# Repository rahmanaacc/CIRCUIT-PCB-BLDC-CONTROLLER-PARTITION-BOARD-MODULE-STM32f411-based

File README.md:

# Modular BLDC Motor Controller Partition Board (STM32F411CEU6 Based)

Projek Capstone ini berfokus pada perancangan hardware modul *controller* motor BLDC (Brushless DC) berbasis mikrokontroler **STM32F411CEU6** menggunakan metode kontrol **6-step commutation (trapezoidal control)**. 

Arsitektur hardware dirancang secara modular (*partition board*) dengan memisahkan domain sinyal kendali, *gate driver*, dan tingkat daya (*inverter stage*). Pemisahan topologi ini bertujuan untuk meminimalkan *noise* switching (EMI), mengoptimalkan manajemen termal, serta mempermudah proses pengujian dan *troubleshooting* secara independen pada tiap modul.

---

## Modul Hardware Utama

Repository ini terdiri dari tiga modul papan terpisah (*partition boards*):

1. **Control-MCU Module (`Control-MCU With Voltage Drop Detector 0,5mm`)**
   * Modul pemroses utama berbasis mikrokontroler **STM32F411CEU6**.
   * Dilengkapi rangkaian *Voltage Drop Detector* dengan lebar jalur *trace* teroptimasi 0,5 mm untuk menjaga integritas sinyal dan stabilitas tegangan referensi MCU.
   * Berfungsi mengolah algoritma **6-step commutation**, membaca sinyal *feedback* posisi rotor, dan menghasilkan sinyal PWM transmisi ke *gate driver*.

2. **Driver & Switching Optimization Circuit (`DRIVER and SWITCHING OPTIMIZATION CIRCUIT REV 2`)**
   * Modul perantara *gate driver* yang mengisolasi sinyal logika kendali level rendah dari tegangan tinggi *inverter*.
   * Mengintegrasikan rangkaian optimasi *switching* untuk mempercepat *rise/fall time* MOSFET, mengurangi *switching loss*, dan mencegah kondisi *cross-conduction* (*shoot-through*).

3. **Inverter Circuit (`INVERTER CIRCUIT REV 2 FIX`)**
   * Modul tingkat daya (*power stage*) berupa jembatan tiga fasa (*three-phase bridge inverter*).
   * Didesain untuk menangani arus tinggi dengan penataan jalur *copper pour* teroptimasi dan konektivitas daya fasa motor yang andal.

---

## Struktur Repository

```text
CIRCUIT-PCB-BLDC-CONTROLLER-PARTITION-BOARD-MODULE-STM32f411-based/
│
├── Control-MCU With Voltage Drop Detector 0,5mm/
│   ├── Control-MCU.kicad_sch          # Skematik KiCad Modul MCU
│   ├── Control-MCU.kicad_pcb          # Layout PCB Modul MCU
│   └── Control-MCU.kicad_pro          # Berkas Proyek KiCad Modul MCU
│
├── DRIVER and SWITCHING OPTIMIZATION CIRCUIT REV 2/
│   ├── DRIVER and SWITCHING OPTIMIZATION CIRCUIT.kicad_sch
│   ├── DRIVER and SWITCHING OPTIMIZATION CIRCUIT.kicad_pcb
│   └── DRIVER and SWITCHING OPTIMIZATION CIRCUIT.kicad_pro
│
├── INVERTER CIRCUIT REV 2 FIX/
│   ├── INVERTER CIRCUIT REV 2 FIX.kicad_sch
│   ├── INVERTER CIRCUIT REV 2 FIX.kicad_pcb
│   └── INVERTER CIRCUIT REV 2 FIX.kicad_pro
│
└── README.md

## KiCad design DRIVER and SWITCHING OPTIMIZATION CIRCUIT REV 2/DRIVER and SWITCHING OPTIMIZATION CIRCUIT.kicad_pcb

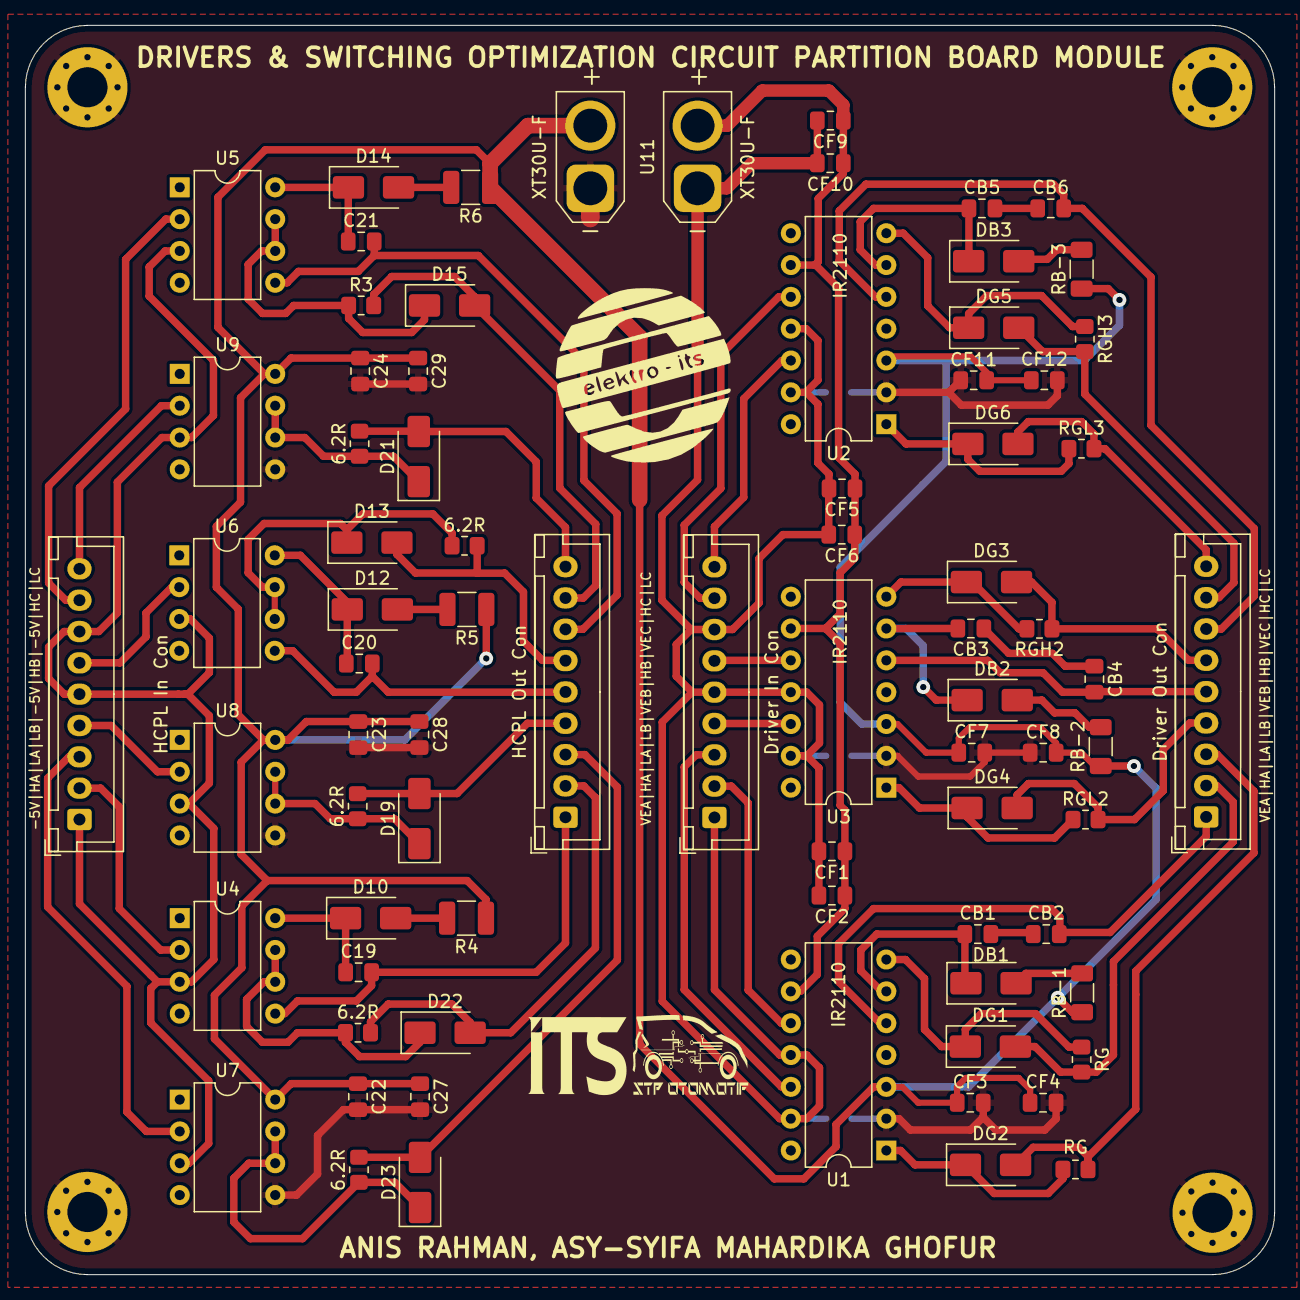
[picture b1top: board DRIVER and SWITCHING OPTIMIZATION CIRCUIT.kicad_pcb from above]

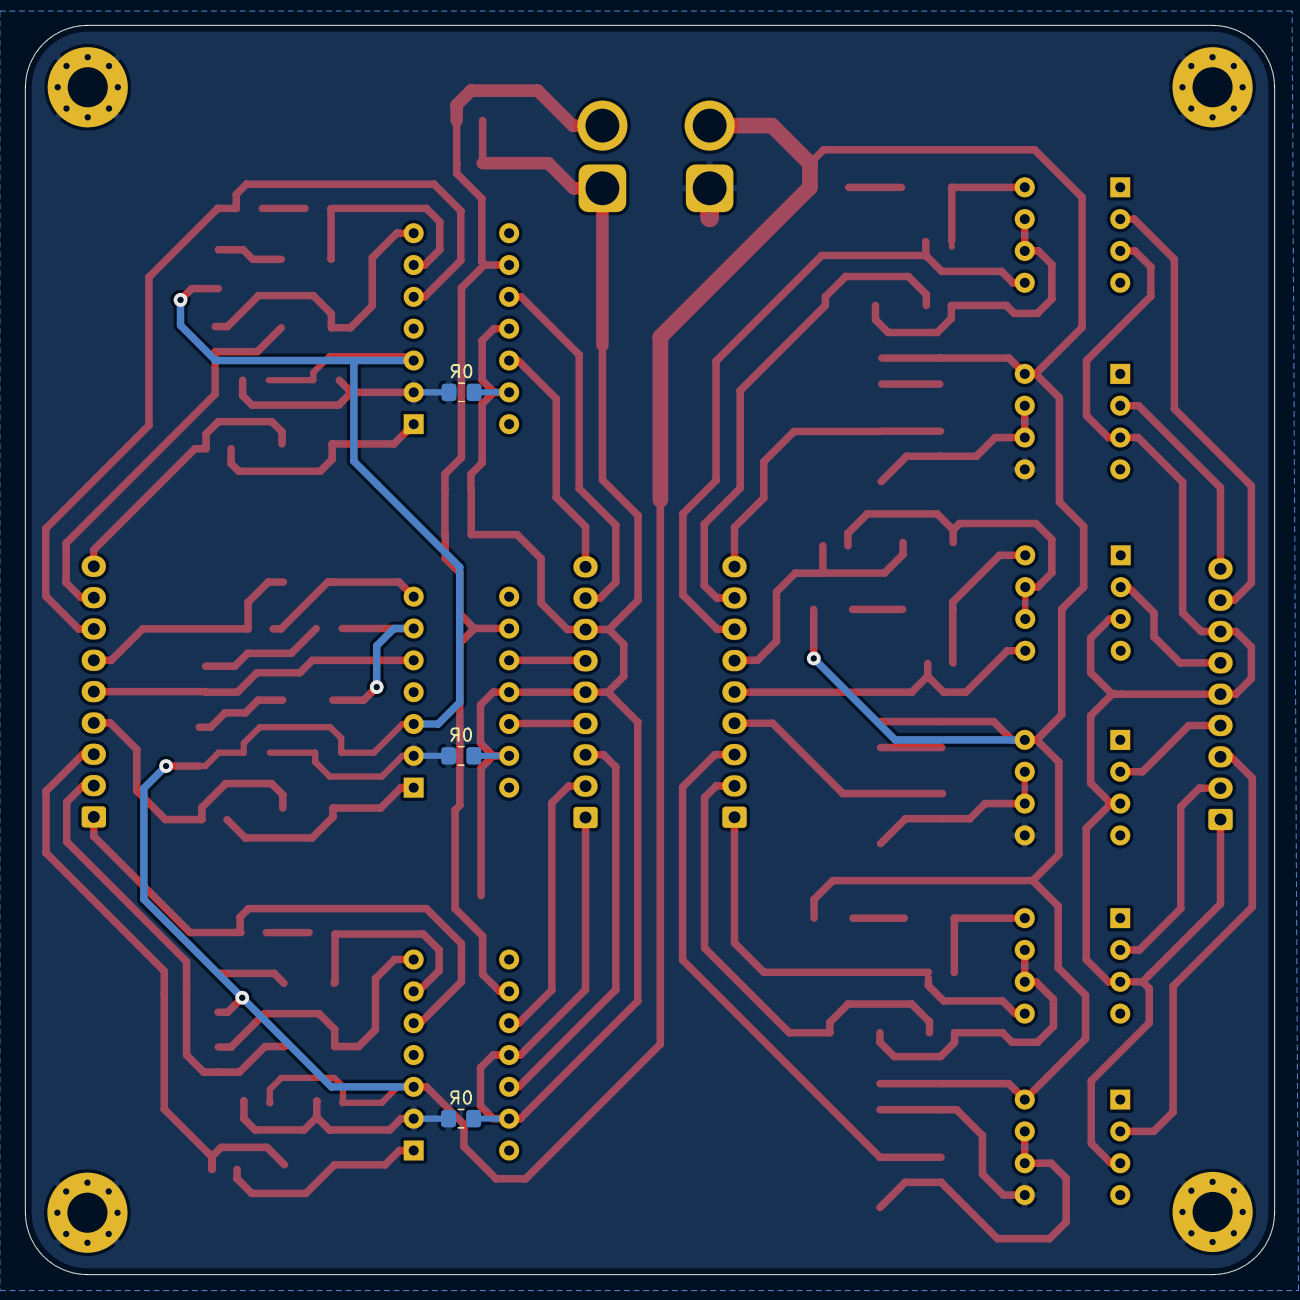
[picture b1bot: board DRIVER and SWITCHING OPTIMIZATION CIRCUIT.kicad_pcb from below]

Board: 2 copper layers, 99.7 x 99.7 mm, 85 parts (3 on the bottom side), 62 nets.

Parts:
C19, C20, C21: 0,22uF; C_0805_2012Metric_Pad1.18x1.45mm_HandSolder
C22, C23, C24: 0,1uF; C_0805_2012Metric_Pad1.18x1.45mm_HandSolder
C27, C28, C29: 10uF; C_0805_2012Metric_Pad1.18x1.45mm_HandSolder
CB1, CB2, CB3, CB4, CB5, CB6: 330nF; C_0805_2012Metric_Pad1.18x1.45mm_HandSolder
CF1, CF4, CF5, CF8, CF9, CF12: 10 uF; C_0805_2012Metric_Pad1.18x1.45mm_HandSolder
CF2, CF3, CF6, CF7, CF10, CF11: 0,1 uF; C_0805_2012Metric_Pad1.18x1.45mm_HandSolder
D10, D12, D13, D14, D15, D19, D21, D22, D23: SS110; D_SMA
DB1, DB2, DB3: SS110; D_SMA
DG1, DG2, DG3, DG4, DG5, DG6: SS110; D_SMA
H1, H2, H3, H4: MountingHole_Pad_MP1; MountingHole_3.2mm_M3_Pad_Via
J1: HCPL In Con; JST_XH_B9B-XH-A_1x09_P2.50mm_Vertical
J2: HCPL Out Con; JST_XH_B9B-XH-A_1x09_P2.50mm_Vertical
J3: Driver In Con; JST_XH_B9B-XH-A_1x09_P2.50mm_Vertical
J4: Driver Out Con; JST_XH_B9B-XH-A_1x09_P2.50mm_Vertical
R0J-1, R0J-2, R0J-3: 0R; R_0805_2012Metric_Pad1.20x1.40mm_HandSolder
R1, R2, R3, R7, R8, R9: 6.2R; R_0805_2012Metric_Pad1.20x1.40mm_HandSolder
R4, R5, R6: 3R; R_1210_3225Metric_Pad1.30x2.65mm_HandSolder
RB-1, RB-2, RB-3: 5,1R; R_1206_3216Metric_Pad1.30x1.75mm_HandSolder
RGH1, RGH2, RGH3: RG; R_0805_2012Metric_Pad1.20x1.40mm_HandSolder
RGL1, RGL2, RGL3: RG; R_0805_2012Metric_Pad1.20x1.40mm_HandSolder
U1, U2, U3: IR2110; DIP-14_W7.62mm
U4, U5, U6, U7, U8, U9: HCPL-3120; DIP-8_W7.62mm
U10, U11: XT30U-F; AMASS_XT30U-F_1x02_P5.0mm_Vertical

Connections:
5V_GND: CF1.2, CF2.2, CF5.2, CF6.2, CF9.2, CF10.2, J3.1, J3.5, J3.7, R0J-1.1, R0J-2.1, R0J-3.1, U1.11 (SD), U1.13 (VSS), U2.11 (SD), U2.13 (VSS), U3.11 (SD), U3.13 (VSS), U11.1 (-)
15V_GND: C22.2, C23.2, C24.2, C27.2, C28.2, C29.2, CF3.2, CF4.2, CF7.2, CF8.2, CF11.2, CF12.2, H1.1, H2.1 (MP), H3.1 (MP), H4.1 (MP), R0J-1.2, R0J-2.2, R0J-3.2, U1.2 (COM), U2.2 (COM), U3.2 (COM), U7.5 (VEE), U8.5 (VEE), U9.5 (VEE), U10.1 (-)
+5V: CF1.1, CF2.1, CF5.1, CF6.1, CF9.1, CF10.1, U1.9 (VDD), U2.9 (VDD), U3.9 (VDD), U11.2 (+)
+15V: C22.1, C23.1, C24.1, C27.1, C28.1, C29.1, CF3.1, CF4.1, CF7.1, CF8.1, CF11.1, CF12.1, R4.1, R5.1, R6.1, RB-1.1, RB-2.1, RB-3.1, U1.3 (VCC), U2.3 (VCC), U3.3 (VCC), U7.8 (VCC), U8.8 (VCC), U9.8 (VCC), U10.2 (+)
-5V: J1.1, J1.5, J1.7, U4.3 (C), U5.3 (C), U6.3 (C), U7.3 (C), U8.3 (C), U9.3 (C)
/HIN A: J1.2, U4.2 (A)
/HIN A DRIVER: J3.2, U1.10 (HIN)
/HIN A HCPL: D22.2 (A2), J2.2, R1.2
/HIN B: J1.6, U6.2 (A)
/HIN B DRIVER: J3.6, U3.10 (HIN)
/HIN B HCPL: D13.2 (A2), J2.6, R2.2
/HIN C: J1.8, U5.2 (A)
/HIN C DRIVER: J3.8, U2.10 (HIN)
/HIN C HCPL: D15.2 (A2), J2.8, R3.2
/High A Driver: DG1.2 (A2), J4.2, RGH1.2
/High B Driver: DG3.2 (A2), J4.6, RGH2.2
/High C Driver: DG5.2 (A2), J4.8, RGH3.2
/LIN A: J1.3, U7.2 (A)
/LIN A DRIVER: J3.3, U1.12 (LIN)
/LIN A HCPL: D23.2 (A2), J2.3, R7.2
/LIN B: J1.4, U8.2 (A)
/LIN B DRIVER: J3.4, U3.12 (LIN)
/LIN B HCPL: D19.2 (A2), J2.4, R8.2
/LIN C: J1.9, U9.2 (A)
/LIN C DRIVER: J3.9, U2.12 (LIN)
/LIN C HCPL: D21.2 (A2), J2.9, R9.2
/Low A Driver: DG2.2 (A2), J4.3, RGL1.2
/Low B Driver: DG4.2 (A2), J4.4, RGL2.2
/Low C Driver: DG6.2 (A2), J4.9, RGL3.2
/VEE A: C19.2, J2.1, U4.5 (VEE)
/VEE B: C20.2, J2.5, U6.5 (VEE)
/VEE C: C21.2, J2.7, U5.5 (VEE)
/VS A Driver: CB2.2, J4.1, U1.5 (VS)
/VS B Driver: CB4.2, J4.5, U3.5 (VS)
/VS C Driver: CB6.2, J4.7, U2.5 (VS)
unnamed: CB1.2, CB2.1
unnamed: CB3.2, CB4.1
unnamed: CB5.2, CB6.1
unnamed: C19.1, D10.1 (A1), U4.8 (VCC)
unnamed: D10.2 (A2), R4.2
unnamed: C20.1, D12.1 (A1), U6.8 (VCC)
unnamed: D12.2 (A2), R5.2
unnamed: D13.1 (A1), R2.1, U6.6 (VO), U6.7 (VO)
unnamed: C21.1, D14.1 (A1), U5.8 (VCC)
unnamed: D14.2 (A2), R6.2
unnamed: D15.1 (A1), R3.1, U5.6 (VO), U5.7 (VO)
unnamed: D19.1 (A1), R8.1, U8.6 (VO), U8.7 (VO)
unnamed: D21.1 (A1), R9.1, U9.6 (VO), U9.7 (VO)
unnamed: D22.1 (A1), R1.1, U4.6 (VO), U4.7 (VO)
unnamed: D23.1 (A1), R7.1, U7.6 (VO), U7.7 (VO)
unnamed: CB1.1, DB1.1 (A1), U1.6 (VB)
unnamed: DB1.2 (A2), RB-1.2
unnamed: CB3.1, DB2.1 (A1), U3.6 (VB)
unnamed: DB2.2 (A2), RB-2.2
unnamed: CB5.1, DB3.1 (A1), U2.6 (VB)
unnamed: DB3.2 (A2), RB-3.2
unnamed: DG1.1 (A1), RGH1.1, U1.7 (HO)
unnamed: DG2.1 (A1), RGL1.1, U1.1 (LO)
unnamed: DG3.1 (A1), RGH2.1, U3.7 (HO)
unnamed: DG4.1 (A1), RGL2.1, U3.1 (LO)
unnamed: DG5.1 (A1), RGH3.1, U2.7 (HO)
unnamed: DG6.1 (A1), RGL3.1, U2.1 (LO)

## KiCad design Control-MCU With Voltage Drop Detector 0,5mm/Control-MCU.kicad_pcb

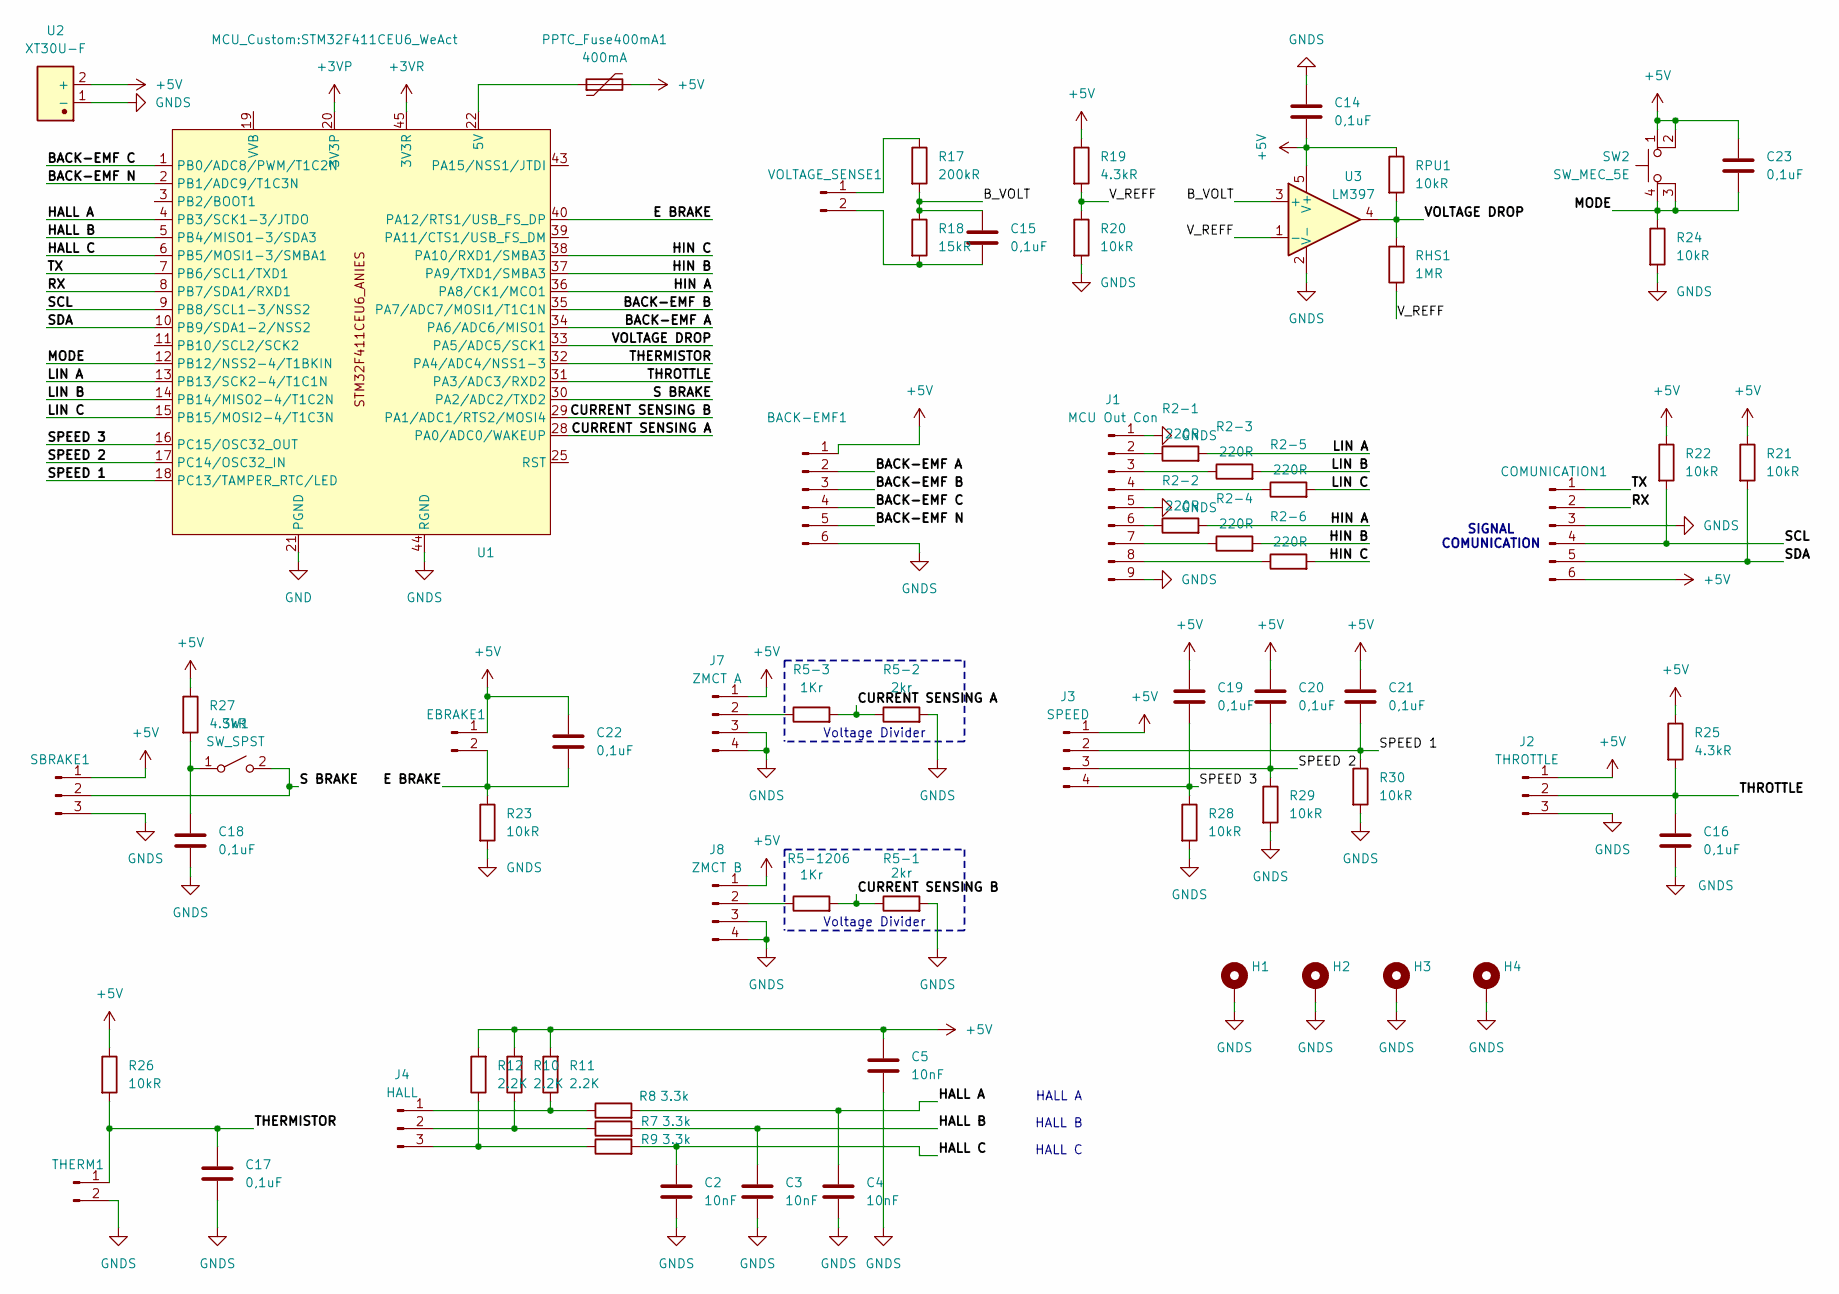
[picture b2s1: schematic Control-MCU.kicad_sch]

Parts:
BACK-EMF1: Conn_01x06_Pin; JST_XH_B6B-XH-A_1x06_P2.50mm_Vertical
C2, C3, C4, C5: 10nF; C_1206_3216Metric_Pad1.33x1.80mm_HandSolder
C14, C15, C16, C17, C18, C19, C20, C21, C22, C23: 0,1uF; C_0805_2012Metric_Pad1.18x1.45mm_HandSolder
COMUNICATION1: Conn_01x06_Pin; JST_XH_B6B-XH-A_1x06_P2.50mm_Vertical
EBRAKE1: EBRAKE; JST_XH_B2B-XH-A_1x02_P2.50mm_Vertical
H1, H2, H3, H4: MountingHole_Pad_MP1; MountingHole_3.2mm_M3_Pad_Via
J1: MCU Out Con; JST_XH_B9B-XH-A_1x09_P2.50mm_Vertical
J2: THROTTLE; JST_XH_B3B-XH-A_1x03_P2.50mm_Vertical
J3: SPEED; JST_XH_B4B-XH-A_1x04_P2.50mm_Vertical
J4: HALL; JST_XH_B3B-XH-A_1x03_P2.50mm_Vertical
J7: ZMCT A; JST_XH_B4B-XH-A_1x04_P2.50mm_Vertical
J8: ZMCT B; JST_XH_B4B-XH-A_1x04_P2.50mm_Vertical
PPTC_Fuse400mA1: 400mA; Fuse_1206_3216Metric_Pad1.42x1.75mm_HandSolder
R2-1, R2-2, R2-3, R2-4, R2-5, R2-6: 220R; R_0805_2012Metric_Pad1.20x1.40mm_HandSolder
R5-1, R5-2: 2kr; R_1206_3216Metric_Pad1.30x1.75mm_HandSolder
R5-3, R5-1206: 1Kr; R_1206_3216Metric_Pad1.30x1.75mm_HandSolder
R7, R8, R9: 3.3k; R_0603_1608Metric_Pad0.98x0.95mm_HandSolder
R10, R11, R12: 2.2K; R_0603_1608Metric_Pad0.98x0.95mm_HandSolder
R17: 200kR; R_0805_2012Metric_Pad1.20x1.40mm_HandSolder
R18: 15kR; R_0805_2012Metric_Pad1.20x1.40mm_HandSolder
R19, R25, R27: 4.3kR; R_0805_2012Metric_Pad1.20x1.40mm_HandSolder
R20, R21, R22, R23, R24, R26, R28, R29, R30: 10kR; R_0805_2012Metric_Pad1.20x1.40mm_HandSolder
RHS1: 1MR; R_0805_2012Metric_Pad1.20x1.40mm_HandSolder
RPU1: 10kR; R_0805_2012Metric_Pad1.20x1.40mm_HandSolder
SBRAKE1: BRAKE; JST_XH_B3B-XH-A_1x03_P2.50mm_Vertical
SW1: SW_SPST; SW_DIP_SPSTx01_Slide_6.7x4.1mm_W7.62mm_P2.54mm_LowProfile
SW2: SW_MEC_5E; SW_PUSH_6mm_H5mm
THERM1: Conn_01x02_Pin; JST_XH_B2B-XH-A_1x02_P2.50mm_Vertical
U1: STM32F411CEU6_WeAct
U2: XT30U-F; AMASS_XT30U-F_1x02_P5.0mm_Vertical; Manufacturer Part XT30U-F
U3: LM397; SOT-23-5
VOLTAGE_SENSE1: VOLTAGE_SENSE; JST_XH_B2B-XH-A_1x02_P2.50mm_Vertical

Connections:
+3VP: U1.20 (3V3P)
+3VR: U1.45 (3V3R)
+5V: BACK-EMF1.1, C5.1, C14.2, C19.1, C20.1, C21.1, C22.1, C23.1, COMUNICATION1.6, EBRAKE1.1, J2.1, J3.1, J7.1, J8.1, PPTC_Fuse400mA1.2, R10.2, R11.2, R12.2, R19.1, R21.1, R22.1, R25.1, R26.1, R27.1, RPU1.1, SBRAKE1.1, SW2.1, SW2.2, U2.2 (+), U3.5 (V+)
/BACK-EMF A: BACK-EMF1.2, U1.34 (PA6/ADC6/MISO1)
/BACK-EMF B: BACK-EMF1.3, U1.35 (PA7/ADC7/MOSI1/T1C1N)
/BACK-EMF C: BACK-EMF1.4, U1.1 (PB0/ADC8/PWM/T1C2N)
/BACK-EMF N: BACK-EMF1.5, U1.2 (PB1/ADC9/T1C3N)
/B_VOLT: C15.1, R17.2, R18.1, U3.3 (+)
/CURRENT SENSING A: R5-2.1, R5-3.2, U1.28 (PA0/ADC0/WAKEUP)
/CURRENT SENSING B: R5-1.1, R5-1206.2, U1.29 (PA1/ADC1/RTS2/MOSI4)
/E BRAKE: C22.2, EBRAKE1.2, R23.1, U1.40 (PA12/RTS1/USB_FS_DP)
/HALL A: C4.1, R8.2, U1.4 (PB3/SCK1-3/JTDO)
/HALL B: C3.1, R7.2, U1.5 (PB4/MISO1-3/SDA3)
/HALL C: C2.1, R9.2, U1.6 (PB5/MOSI1-3/SMBA1)
/HIN A: R2-2.2, U1.36 (PA8/CK1/MCO1)
/HIN B: R2-4.2, U1.37 (PA9/TXD1/SMBA3)
/HIN C: R2-6.2, U1.38 (PA10/RXD1/SMBA3)
/LIN A: R2-1.2, U1.13 (PB13/SCK2-4/T1C1N)
/LIN B: R2-3.2, U1.14 (PB14/MISO2-4/T1C2N)
/LIN C: R2-5.2, U1.15 (PB15/MOSI2-4/T1C3N)
/MODE: C23.2, R24.1, SW2.3 (K), SW2.4 (A), U1.12 (PB12/NSS2-4/T1BKIN)
/RX: COMUNICATION1.2, U1.8 (PB7/SDA1/RXD1)
/S BRAKE: SBRAKE1.2, SW1.2 (B), U1.30 (PA2/ADC2/TXD2)
/SCL: COMUNICATION1.4, R22.2, U1.9 (PB8/SCL1-3/NSS2)
/SDA: COMUNICATION1.5, R21.2, U1.10 (PB9/SDA1-2/NSS2)
/SPEED 1: C21.2, J3.2, R30.1, U1.18 (PC13/TAMPER_RTC/LED)
/SPEED 2: C20.2, J3.3, R29.1, U1.17 (PC14/OSC32_IN)
/SPEED 3: C19.2, J3.4, R28.1, U1.16 (PC15/OSC32_OUT)
/THERMISTOR: C17.1, R26.2, THERM1.1, U1.32 (PA4/ADC4/NSS1-3)
/THROTTLE: C16.1, J2.2, R25.2, U1.31 (PA3/ADC3/RXD2)
/TX: COMUNICATION1.1, U1.7 (PB6/SCL1/TXD1)
/VOLTAGE DROP: RHS1.2, RPU1.2, U1.33 (PA5/ADC5/SCK1), U3.4
/V_REFF: R19.2, R20.1, RHS1.1, U3.1 (-)
GND: U1.21 (PGND)
GNDS: BACK-EMF1.6, C2.2, C3.2, C4.2, C5.2, C14.1, C16.2, C17.2, C18.2, COMUNICATION1.3, H1.1, H2.1, H3.1, H4.1, J1.1, J1.5, J1.9, J2.3, J7.3, J7.4, J8.3, J8.4, R5-1.2, R5-2.2, R20.2, R23.2, R24.2, R28.2, R29.2, R30.2, SBRAKE1.3, THERM1.2, U1.44 (RGND), U2.1 (-), U3.2 (V-)
unnamed: J1.2, R2-1.1
unnamed: J1.3, R2-3.1
unnamed: J1.4, R2-5.1
unnamed: J1.6, R2-2.1
unnamed: J1.7, R2-4.1
unnamed: J1.8, R2-6.1
unnamed: J4.1, R8.1, R11.1
unnamed: J4.2, R7.1, R10.1
unnamed: J4.3, R9.1, R12.1
unnamed: J7.2, R5-3.1
unnamed: J8.2, R5-1206.1
unnamed: C18.1, R27.2, SW1.1 (A)
unnamed: PPTC_Fuse400mA1.1, U1.22 (5V)
unnamed: R17.1, VOLTAGE_SENSE1.1
unnamed: C15.2, R18.2, VOLTAGE_SENSE1.2

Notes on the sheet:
Voltage Divider
HALL C
HALL A
HALL B
SIGNAL COMUNICATION

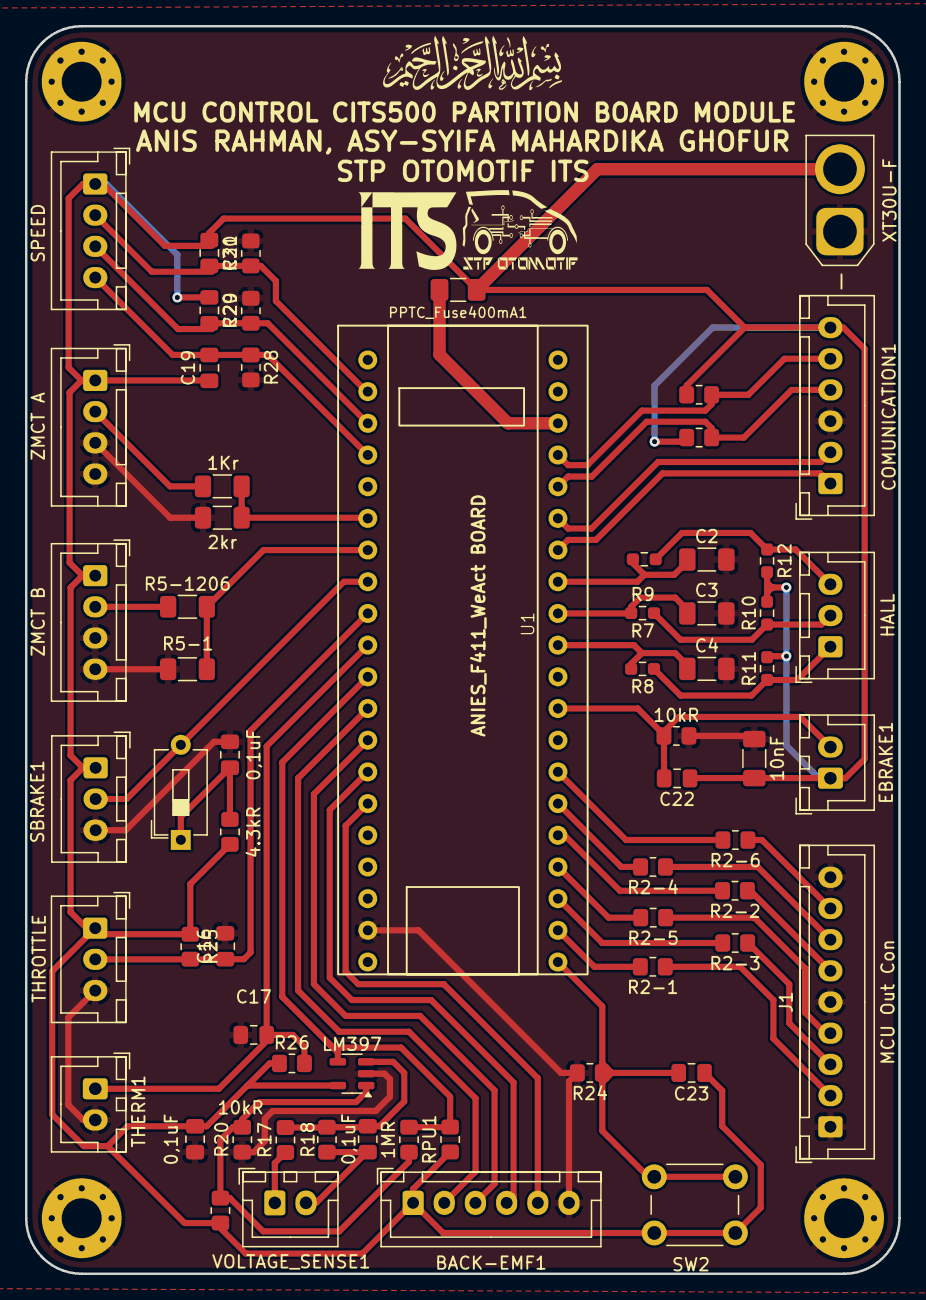
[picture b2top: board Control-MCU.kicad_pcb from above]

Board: 2 copper layers, 70.0 x 100.0 mm, 68 parts (0 on the bottom side), 47 nets.

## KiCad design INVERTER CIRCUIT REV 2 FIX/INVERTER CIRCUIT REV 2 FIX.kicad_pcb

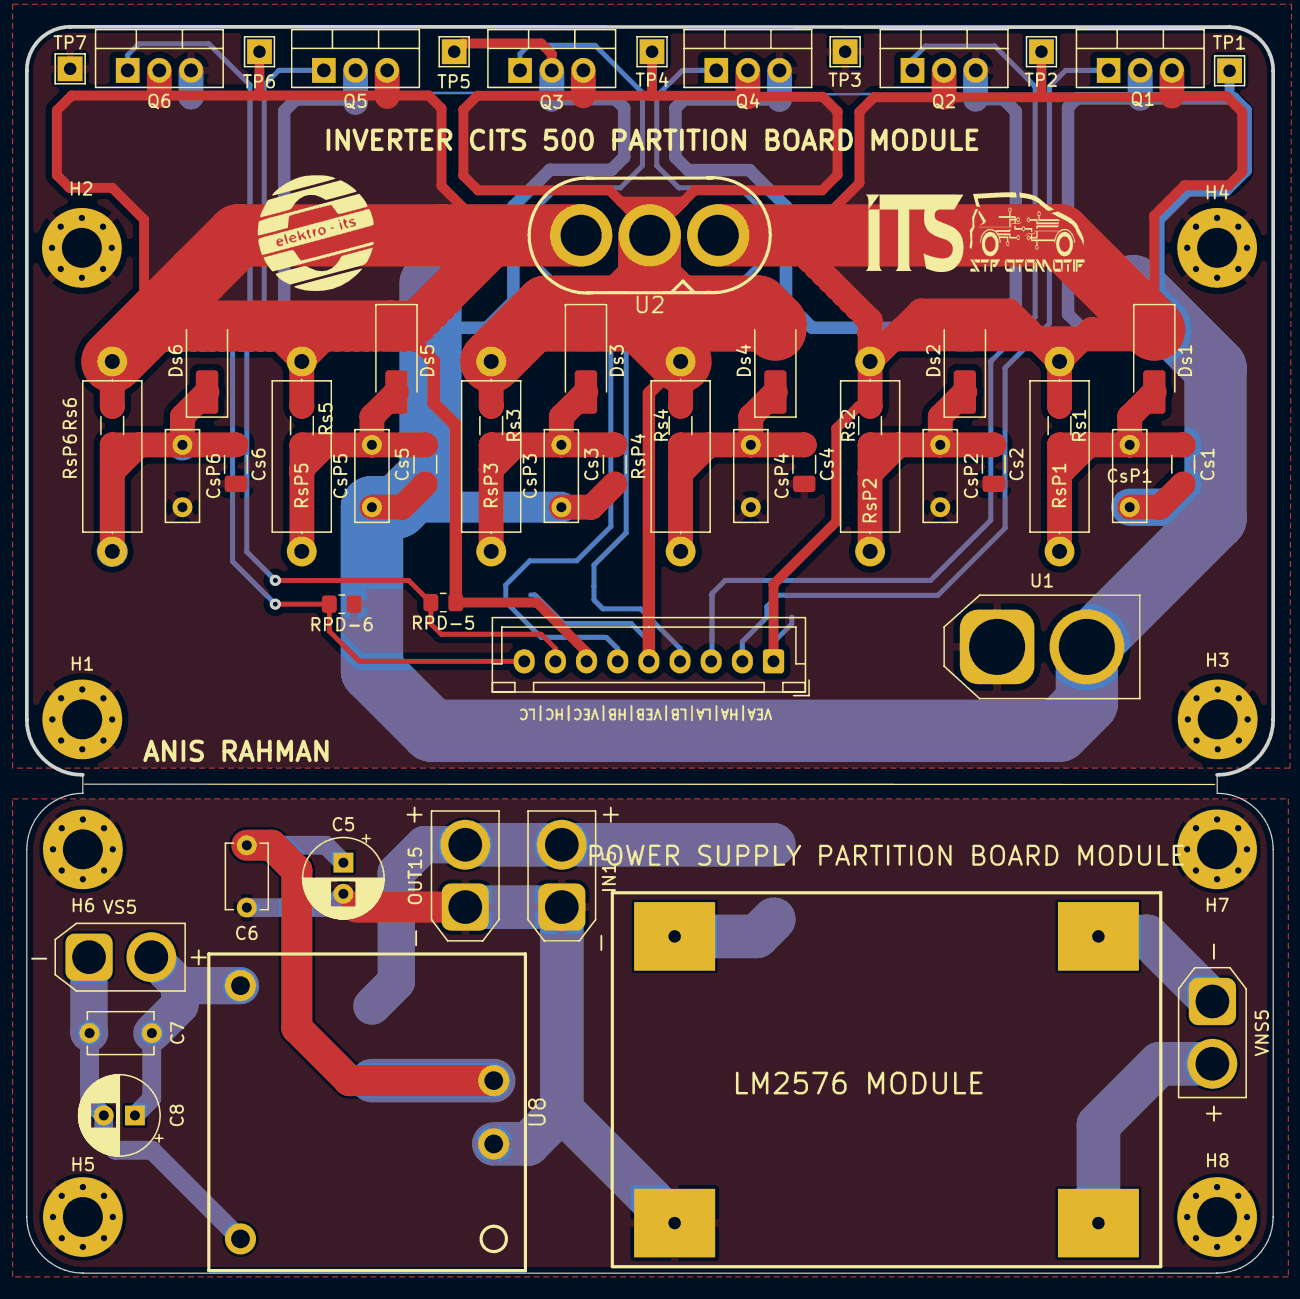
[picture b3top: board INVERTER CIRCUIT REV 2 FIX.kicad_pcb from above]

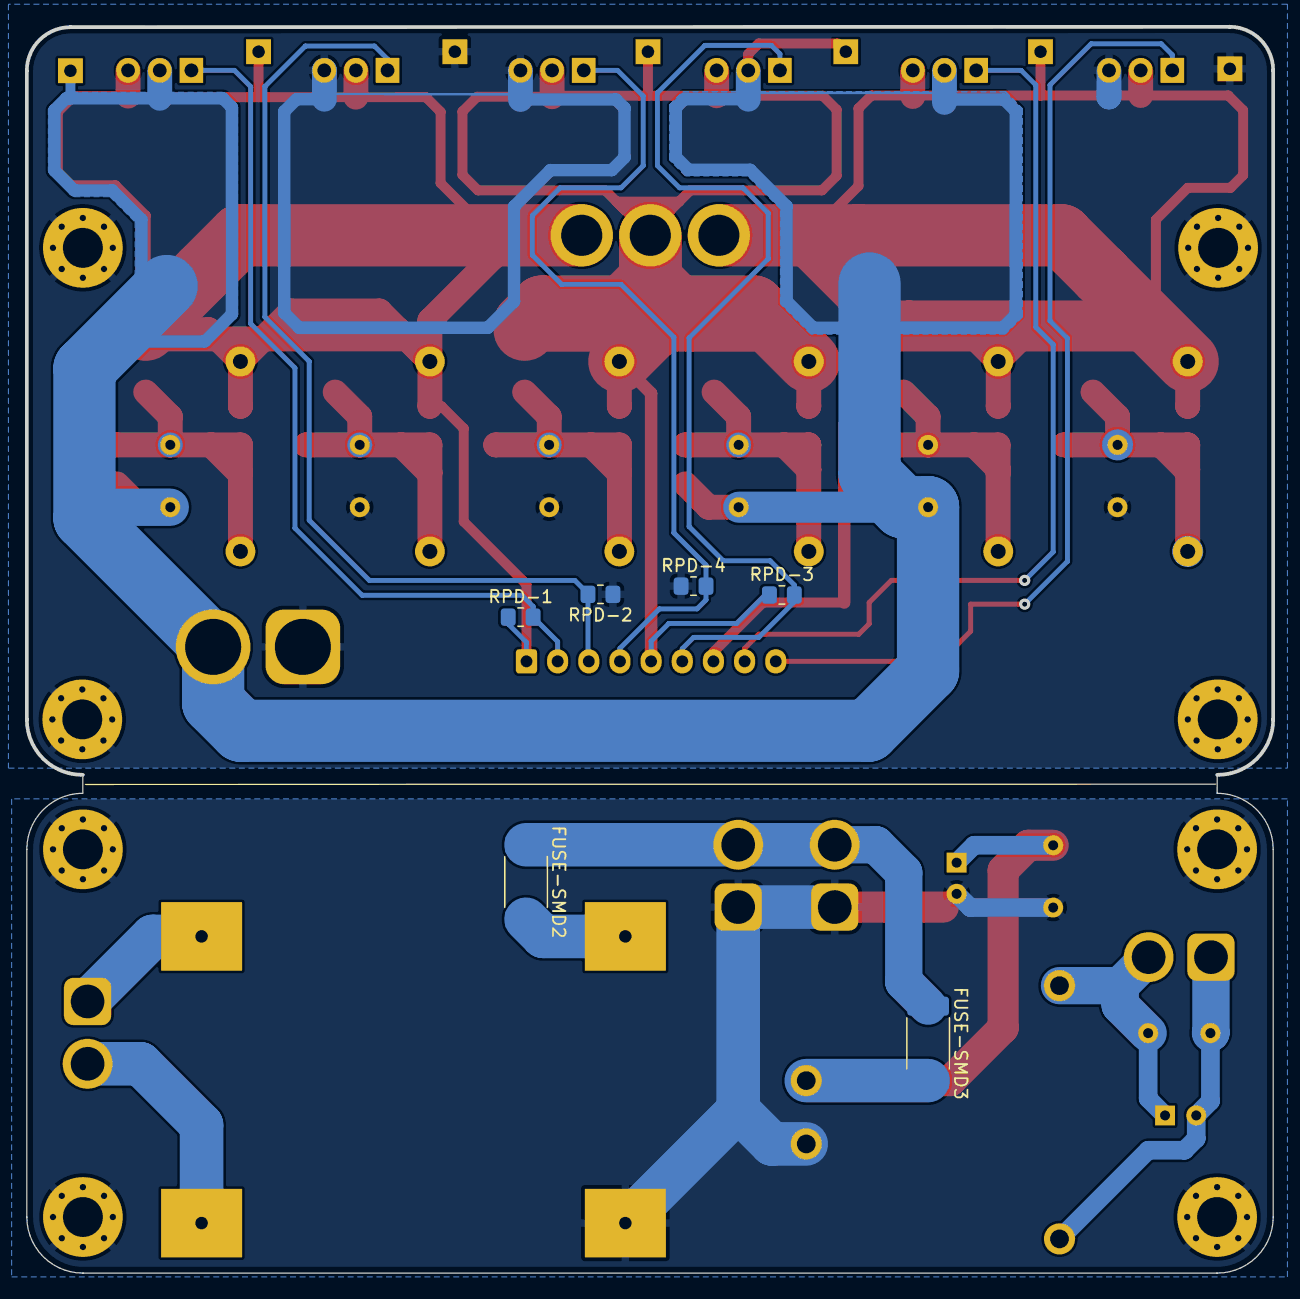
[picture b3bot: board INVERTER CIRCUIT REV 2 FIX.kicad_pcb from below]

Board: 2 copper layers, 100.0 x 100.0 mm, 72 parts (6 on the bottom side), 25 nets.

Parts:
C5, C8: ELCO 220 uF; CP_Radial_D6.3mm_P2.50mm
C6, C7: CERAMIC 100 nF; C_Disc_D5.1mm_W3.2mm_P5.00mm
Cs1, Cs2, Cs3, Cs4, Cs5, Cs6: 4.7nF; C_1206_3216Metric_Pad1.33x1.80mm_HandSolder
CsP1, CsP2, CsP3, CsP4, CsP5, CsP6: 4.7nF; C_Rect_L7.2mm_W2.5mm_P5.00mm_FKS2_FKP2_MKS2_MKP2
Ds1, Ds2, Ds3, Ds4, Ds5, Ds6: SS110; D_SMA_Handsoldering
FUSE-SMD2, FUSE-SMD3: 5A; Fuse_2512_6332Metric_Pad1.52x3.35mm_HandSolder
H1, H2, H3, H4, H5, H6, H7, H8: MountingHole_Pad_MP1; MountingHole_3.2mm_M3_Pad_Via
IN15: XT30U-IN; AMASS_XT30U-F_1x02_P5.0mm_Vertical
J1: Inverter In Con; JST_XH_B9B-XH-A_1x09_P2.50mm_Vertical
MOD2: LM2576 MODULE
OUT15: XT30U-OUT; AMASS_XT30U-F_1x02_P5.0mm_Vertical
Q1, Q2, Q3, Q4, Q5, Q6: TK100E10N1,S1X(S; TO-220-3_Vertical
RPD-1, RPD-2, RPD-3, RPD-4, RPD-5, RPD-6: 10K; R_0805_2012Metric_Pad1.20x1.40mm_HandSolder
Rs1, Rs2, Rs3, Rs4, Rs5, Rs6: 3K; R_1206_3216Metric_Pad1.30x1.75mm_HandSolder
RsP1, RsP2, RsP3, RsP4, RsP5, RsP6: 3k3; R_Axial_DIN0414_L11.9mm_D4.5mm_P15.24mm_Horizontal
TP1, TP2, TP3, TP4, TP5, TP6, TP7: TestPoint; TestPoint_THTPad_2.0x2.0mm_Drill1.0mm
U1: XT60U-F; AMASS_XT60-M_1x02_P7.20mm_Vertical
U2: MR30航模插头3P公头; CONN-TH_3P_MR60PB-M
U8: VRB2405YMD-6WR3
VNS5: XT30U-OUTNS; AMASS_XT30U-F_1x02_P5.0mm_Vertical
VS5: XT30U-OUT; AMASS_XT30U-F_1x02_P5.0mm_Vertical

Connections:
/+5V: C7.1, C8.1, U8.3 (+VO), VS5.2 (+)
/+5V NS: MOD2.3 (OUT+), VNS5.2 (+)
/+V15: FUSE-SMD2.1, FUSE-SMD3.1, IN15.2 (+), OUT15.2 (+)
/+VBATT: Cs1.1, Cs3.1, Cs5.1, CsP1.1, CsP3.1, CsP5.1, Q1.2 (D), Q3.2 (D), Q5.2 (D), TP1.1, TP5.1, U1.2 (+)
/-5V: C7.2, C8.2, U8.5 (0V), VS5.1 (-)
/-5V NS: MOD2.4 (OUT-), VNS5.1 (-)
/-V15: C5.2, C6.2, H5.1, H6.1, H7.1, H8.1, IN15.1 (-), MOD2.2 (IN-), OUT15.1 (-), U8.1 (GND)
/-VBATT: Cs2.2, Cs4.2, Cs6.2, CsP2.2, CsP4.2, CsP6.2, H1.1, H2.1, H3.1, H4.1, Q2.3 (S), Q4.3 (S), Q6.3 (S), RPD-2.1, RPD-4.1, RPD-6.1, TP3.1, TP7.1, U1.1 (-)
/Gate High A: J1.2, Q1.1 (G), RPD-1.2
/Gate High B: J1.6, Q3.1 (G), RPD-3.2
/Gate High C: J1.8, Q5.1 (G), RPD-5.2
/Gate Low A: J1.3, Q2.1 (G), RPD-2.2
/Gate Low B: J1.4, Q4.1 (G), RPD-4.2
/Gate Low C: J1.9, Q6.1 (G), RPD-6.2
/PHASE A: Ds1.1 (K), Ds2.2 (A), J1.1, Q1.3 (S), Q2.2 (D), RPD-1.1, Rs1.1, Rs2.2, RsP1.1, RsP2.2, TP2.1, U2.1
/PHASE B: Ds3.1 (K), Ds4.2 (A), J1.5, Q3.3 (S), Q4.2 (D), RPD-3.1, Rs3.1, Rs4.2, RsP3.1, RsP4.2, TP4.1, U2.2
/PHASE C: Ds5.1 (K), Ds6.2 (A), J1.7, Q5.3 (S), Q6.2 (D), RPD-5.1, Rs5.1, Rs6.2, RsP5.1, RsP6.2, TP6.1, U2.3
unnamed: Cs1.2, CsP1.2, Ds1.2 (A), Rs1.2, RsP1.2
unnamed: Cs2.1, CsP2.1, Ds2.1 (K), Rs2.1, RsP2.1
unnamed: Cs3.2, CsP3.2, Ds3.2 (A), Rs3.2, RsP3.2
unnamed: Cs4.1, CsP4.1, Ds4.1 (K), Rs4.1, RsP4.1
unnamed: Cs5.2, CsP5.2, Ds5.2 (A), Rs5.2, RsP5.2
unnamed: Cs6.1, CsP6.1, Ds6.1 (K), Rs6.1, RsP6.1
unnamed: FUSE-SMD2.2, MOD2.1 (IN+)
unnamed: C5.1, C6.1, FUSE-SMD3.2, U8.2 (VIN)
